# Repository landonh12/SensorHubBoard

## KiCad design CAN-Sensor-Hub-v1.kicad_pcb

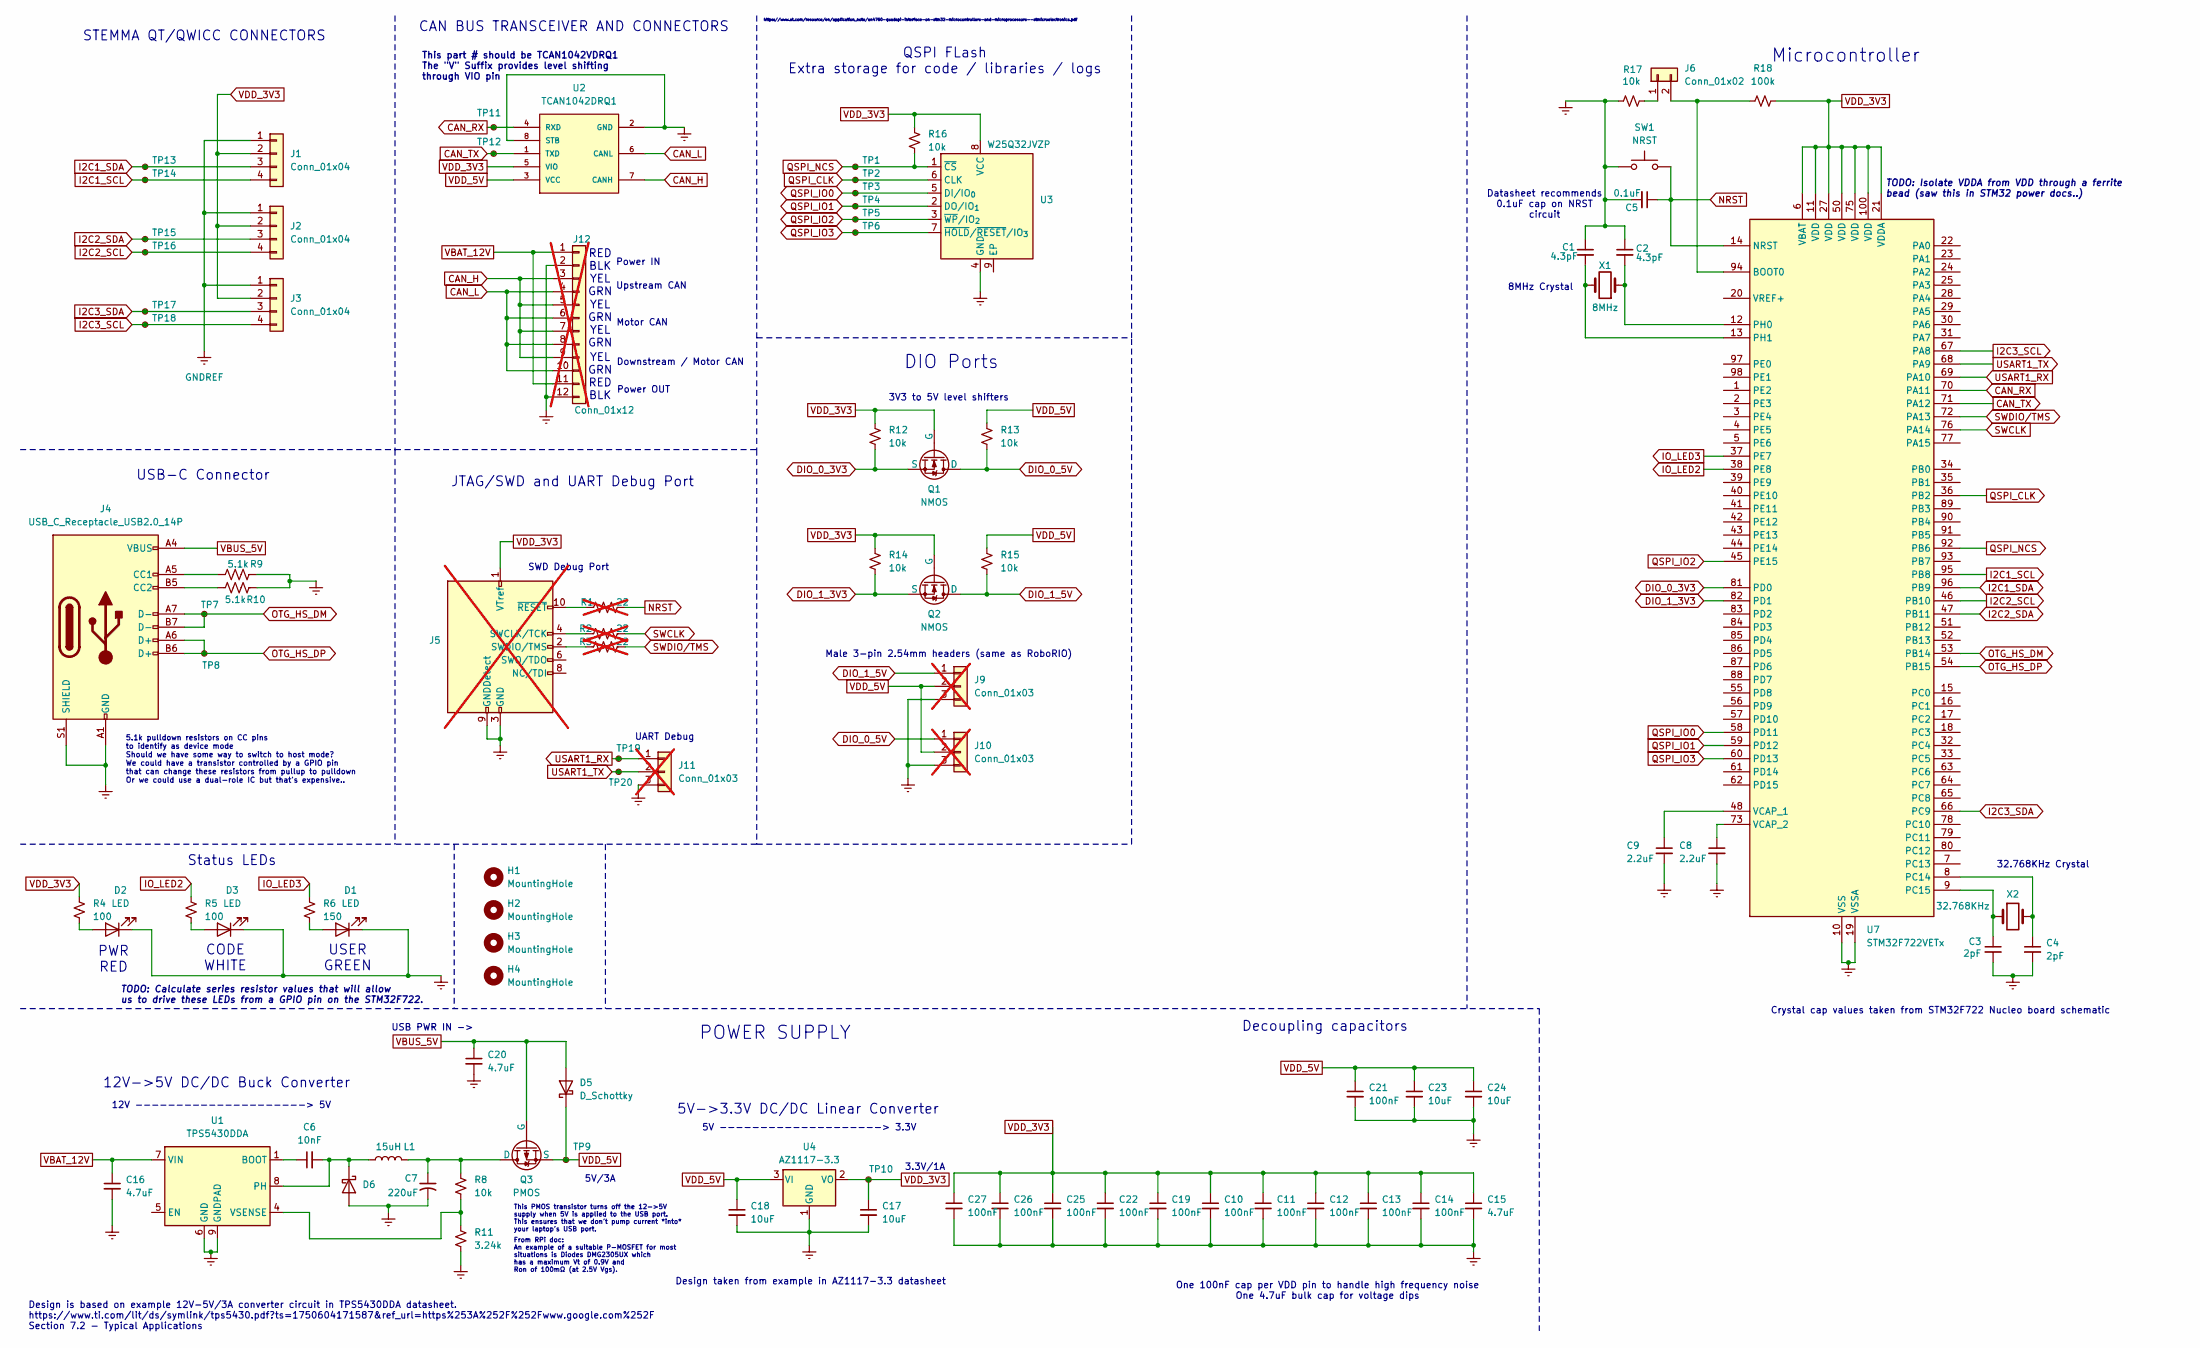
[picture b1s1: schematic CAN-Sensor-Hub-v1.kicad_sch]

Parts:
C1, C2: 4.3pF; C_0402_1005Metric; LCSC CL05C100JB5NNNC
C3, C4: 2pF; C_0402_1005Metric; LCSC 0402CG2R0C500NT
C5: 0.1uF; C_0402_1005Metric; LCSC CL05B104KO5NNNC
C6: 10nF; C_0402_1005Metric; LCSC CL05B103KB5NNNC
C7: 220uF; CP_EIA-3528-21_Kemet-B
C8, C9: 2.2uF; C_0402_1005Metric; LCSC CL05A225MQ5NSNC
C10, C11, C12, C13, C14, C19, C21, C22, C25, C26, C27: 100nF; C_0402_1005Metric; LCSC CL05B104KO5NNNC
C15, C20: 4.7uF; C_0603_1608Metric; LCSC CL10A475KO8NNNC
C16: 4.7uF; C_0805_2012Metric; LCSC CL21A475KAQNNNE
C17, C18, C23, C24: 10uF; C_0603_1608Metric; LCSC CL10A106MA8NRNC
D1: LED; LED_0805_2012Metric; LCSC KT-0805G
D2: LED; LED_0805_2012Metric; LCSC NCD0805R1
D3: LED; LED_0805_2012Metric; LCSC KT-0805W
D5, D6: D_Schottky; D_0603_1608Metric; LCSC SD0603S040S0R2
H1, H2, H3, H4: MountingHole; MountingHole_2.7mm_M2.5
J1, J2, J3: Conn_01x04; JST_SH_SM04B-SRSS-TB_1x04-1MP_P1.00mm_Horizontal; LCSC SM04B-SRSS-TB(LF)(SN)
J4: USB_C_Receptacle_USB2.0_14P; USB_C_Receptacle_GCT_USB4110; LCSC TYPEC-304YSSW-ACP16
J5: Conn_ARM_JTAG_SWD_10; PinHeader_2x05_P1.27mm_Vertical_SMD; not fitted
J6: Conn_01x02; PinHeader_1x02_P2.54mm_Vertical
J9, J10: Conn_01x03; PinHeader_1x03_P2.54mm_Horizontal; not fitted
J11: Conn_01x03; PinHeader_1x03_P2.54mm_Vertical; not fitted
J12: Conn_01x12; TerminalBlock_WAGO_2601-1112_1x12_P3.50mm_Horizontal; not fitted
L1: 15uH; L_Sumida_CDMC6D28_7.25x6.5mm; LCSC CYA0650-15UH
Q1, Q2: NMOS; SOT-23; LCSC SI2301CDS-T1-GE3
Q3: PMOS; SOT-23; LCSC AO3401A
R1, R2, R3: 22; R_0805_2012Metric; not fitted
R4, R5: 100; R_0402_1005Metric; LCSC 0402WGF1000TCE
R6: 150; R_0402_1005Metric; LCSC 0402WGF1500TCE
R8, R12, R13, R14, R15, R17: 10k; R_0402_1005Metric; LCSC 0402WGF1002TCE
R9, R10: 5.1k; R_0402_1005Metric; LCSC 0402WGF5101TCE
R11: 3.24k; R_0402_1005Metric; LCSC 0402WGF3241TCE
R16: 10k; R_0402_1005Metric
R18: 100k; R_0402_1005Metric; LCSC 0402WGF1002TCE
SW1: NRST; SW_TS-1088-AR02016; LCSC TS-1088-AR02016
TP1, TP2, TP3, TP4, TP5, TP6, TP7, TP8, TP9, TP10, TP11, TP12, TP13, TP14, TP15, TP16, TP17, TP18, TP19, TP20: TestPoint_Small; TestPoint_Pad_D0.5mm
U1: TPS5430DDA; TI_SO-PowerPAD-8_ThermalVias; LCSC TPS5430DDAR
U2: TCAN1042DRQ1; SOIC-8_3.9x4.9mm_P1.27mm; PARTNUMBER TCAN1042DRQ1
U3: W25Q32JVZP; WSON-8-1EP_6x5mm_P1.27mm_EP3.4x4.3mm; LCSC W25Q32JVZPIQ
U4: AZ1117-3.3; SOT-223-3_TabPin2; LCSC AMS1117-3.3
U7: STM32F722VETx; LQFP-100_14x14mm_P0.5mm; LCSC STM32F722VET6
X1: 8MHz; Crystal_SMD_3225-2Pin_3.2x2.5mm; LCSC NX3225GD-8MHZ-STD-CRA-3
X2: 32.768KHz; Crystal_SMD_3215-2Pin_3.2x1.5mm; LCSC NX3215SA-32.768K-STD-MUA-14

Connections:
CAN_H: J12.3, J12.5, J12.7, J12.9, U2.7 (CANH)
CAN_L: J12.4, J12.6, J12.8, J12.10, U2.6 (CANL)
CAN_RX: TP11.1, U2.4 (RXD), U7.70 (PA11)
CAN_TX: TP12.1, U2.1 (TXD), U7.71 (PA12)
DIO_0_3V3: Q1.3 (S), R12.2, U7.81 (PD0)
DIO_0_5V: J10.1, Q1.1 (D), R13.2
DIO_1_3V3: Q2.3 (S), R14.2, U7.82 (PD1)
DIO_1_5V: J9.1, Q2.1 (D), R15.2
GNDREF: C1.1, C2.1, C3.2, C4.2, C5.2, C7.2, C8.2, C9.2, C10.2, C11.2, C12.2, C13.2, C14.2, C15.2, C16.2, C17.2, C18.2, C19.2, C20.2, C21.2, C22.2, C23.2, C24.2, C25.2, C26.2, C27.2, D1.1 (K), D2.1 (K), D3.1 (K), D6.2 (A), J1.1, J2.1, J3.1, J4.A1 (GND), J4.A12 (GND), J4.B1 (GND), J4.B12 (GND), J4.S1 (SHIELD), J5.3 (GND), J5.5 (GND), J5.9 (GNDDetect), J9.3, J10.3, J11.3, J12.2, J12.12, R9.2, R10.2, R11.2, R17.1, SW1.1, U1.6 (GND), U1.9 (GNDPAD), U2.2 (GND), U2.8 (STB), U3.4 (GND), U4.1 (GND), U7.10 (VSS), U7.19 (VSSA), U7.26 (VSS), U7.49 (VSS), U7.74 (VSS), U7.99 (VSS)
I2C1_SCL: J1.4, TP14.1, U7.95 (PB8)
I2C1_SDA: J1.3, TP13.1, U7.96 (PB9)
I2C2_SCL: J2.4, TP16.1, U7.46 (PB10)
I2C2_SDA: J2.3, TP15.1, U7.47 (PB11)
I2C3_SCL: J3.4, TP18.1, U7.67 (PA8)
I2C3_SDA: J3.3, TP17.1, U7.66 (PC9)
IO_LED1: U7.39 (PE9)
IO_LED2: R5.1, U7.38 (PE8)
IO_LED3: R6.1, U7.37 (PE7)
NRST: C5.1, R1.2, SW1.2, U7.14 (NRST)
unnamed: D1.2 (A), R6.2
unnamed: D2.2 (A), R4.2
unnamed: D3.2 (A), R5.2
unnamed: C6.2, D6.1 (K), L1.1, U1.8 (PH)
unnamed: J4.A5 (CC1), R9.1
unnamed: J4.B5 (CC2), R10.1
unnamed: J5.4 (SWCLK/TCK), R2.1
unnamed: J5.2 (SWDIO/TMS), R3.1
unnamed: J5.10 (~RESET), R1.1
unnamed: J6.1, R17.2
unnamed: J6.2, R18.1, U7.94 (BOOT0)
unnamed: C7.1, L1.2, Q3.1 (D), R8.1
unnamed: C6.1, U1.1 (BOOT)
unnamed: R8.2, R11.1, U1.4 (VSENSE)
unnamed: C4.1, U7.8 (PC14), X2.2
unnamed: C3.1, U7.9 (PC15), X2.1
unnamed: C2.2, U7.12 (PH0), X1.1
unnamed: C1.2, U7.13 (PH1), X1.2
unnamed: C9.1, U7.48 (VCAP_1)
unnamed: C8.1, U7.73 (VCAP_2)
OTG_HS_DM: J4.A7 (D-), J4.B7 (D-), TP7.1, U7.53 (PB14)
OTG_HS_DP: J4.A6 (D+), J4.B6 (D+), TP8.1, U7.54 (PB15)
QSPI_CLK: TP2.1, U3.6 (CLK), U7.36 (PB2)
QSPI_IO0: TP3.1, U3.5 (DI/IO_{0}), U7.58 (PD11)
QSPI_IO1: TP4.1, U3.2 (DO/IO_{1}), U7.59 (PD12)
QSPI_IO2: TP5.1, U3.3 (~WP/IO_{2}), U7.45 (PE15)
QSPI_IO3: TP6.1, U3.7 (~HOLD/~RESET/IO_{3}), U7.60 (PD13)
QSPI_NCS: R16.2, TP1.1, U3.1 (~CS), U7.92 (PB6)
SWCLK: R2.2, U7.76 (PA14)
SWDIO/TMS: R3.2, U7.72 (PA13)
USART1_RX: J11.1, TP19.1, U7.69 (PA10)
USART1_TX: J11.2, TP20.1, U7.68 (PA9)
VBAT_12V: C16.1, J12.1, J12.11, U1.7 (VIN)
VBUS_5V: C20.1, D5.2 (A), J4.A4 (VBUS), J4.A9 (VBUS), J4.B4 (VBUS), J4.B9 (VBUS), Q3.2 (G)
VDD_3V3: C10.1, C11.1, C12.1, C13.1, C14.1, C15.1, C17.1, C19.1, C22.1, C25.1, C26.1, C27.1, J1.2, J2.2, J3.2, J5.1 (VTref), Q1.2 (G), Q2.2 (G), R4.1, R12.1, R14.1, R16.1, R18.2, TP10.1, U2.5 (VIO), U3.8 (VCC), U4.2 (VO), U7.6 (VBAT), U7.11 (VDD), U7.21 (VDDA), U7.27 (VDD), U7.50 (VDD), U7.75 (VDD), U7.100 (VDD)
VDD_5V: C18.1, C21.1, C23.1, C24.1, D5.1 (K), J9.2, J10.2, Q3.3 (S), R13.1, R15.1, TP9.1, U2.3 (VCC), U4.3 (VI)

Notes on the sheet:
Datasheet recommends 0.1uF cap on NRST circuit
Microcontroller
8MHz Crystal
3V3 to 5V level shifters
5V --------------------> 3.3V
Motor CAN
Decoupling capacitors
YEL GRN RED BLK
USB-C Connector
Power OUT
PWR RED
12V ---------------------> 5V
5.1k pulldown resistors on CC pins to identify as device mode Should we have some way to switch to host mode? We could have a transistor controlled by a GPIO pin that can change these resistors from pullup to pulldown Or we could use a dual-role IC but that's expensive..
Status LEDs
TODO: Isolate VDDA from VDD through a ferrite bead (saw this in STM32 power docs..)
UART Debug
One 100nF cap per VDD pin to handle high frequency noise One 4.7uF bulk cap for voltage dips
RED BLK YEL GRN
Power IN
Design is based on example 12V-5V/3A converter circuit in TPS5430DDA datasheet. https://www.ti.com/lit/ds/symlink/tps5430.pdf?ts=1750604171587&ref_url=https%253A%252F%252Fwww.google.com%252F Section 7.2 - Typical Applications
USB PWR IN ->
This PMOS transistor turns off the 12->5V supply when 5V is applied to the USB port. This ensures that we don't pump current *into* your laptop's USB port.
STEMMA QT/QWICC CONNECTORS
CODE WHITE
This part # should be TCAN1042VDRQ1 The "V" Suffix provides level shifting through VIO pin
DIO Ports
QSPI FLash Extra storage for code / libraries / logs
3.3V/1A
Design taken from example in AZ1117-3.3 datasheet
CAN BUS TRANSCEIVER AND CONNECTORS
32.768KHz Crystal
5V->3.3V DC/DC Linear Converter
USER GREEN
https://www.st.com/resource/en/application_note/an4760-quadspi-interface-on-stm32-microcontrollers-and-microprocessors--stmicroelectronics.pdf
YEL GRN YEL GRN
5V/3A
POWER SUPPLY
JTAG/SWD and UART Debug Port
Upstream CAN
Downstream / Motor CAN

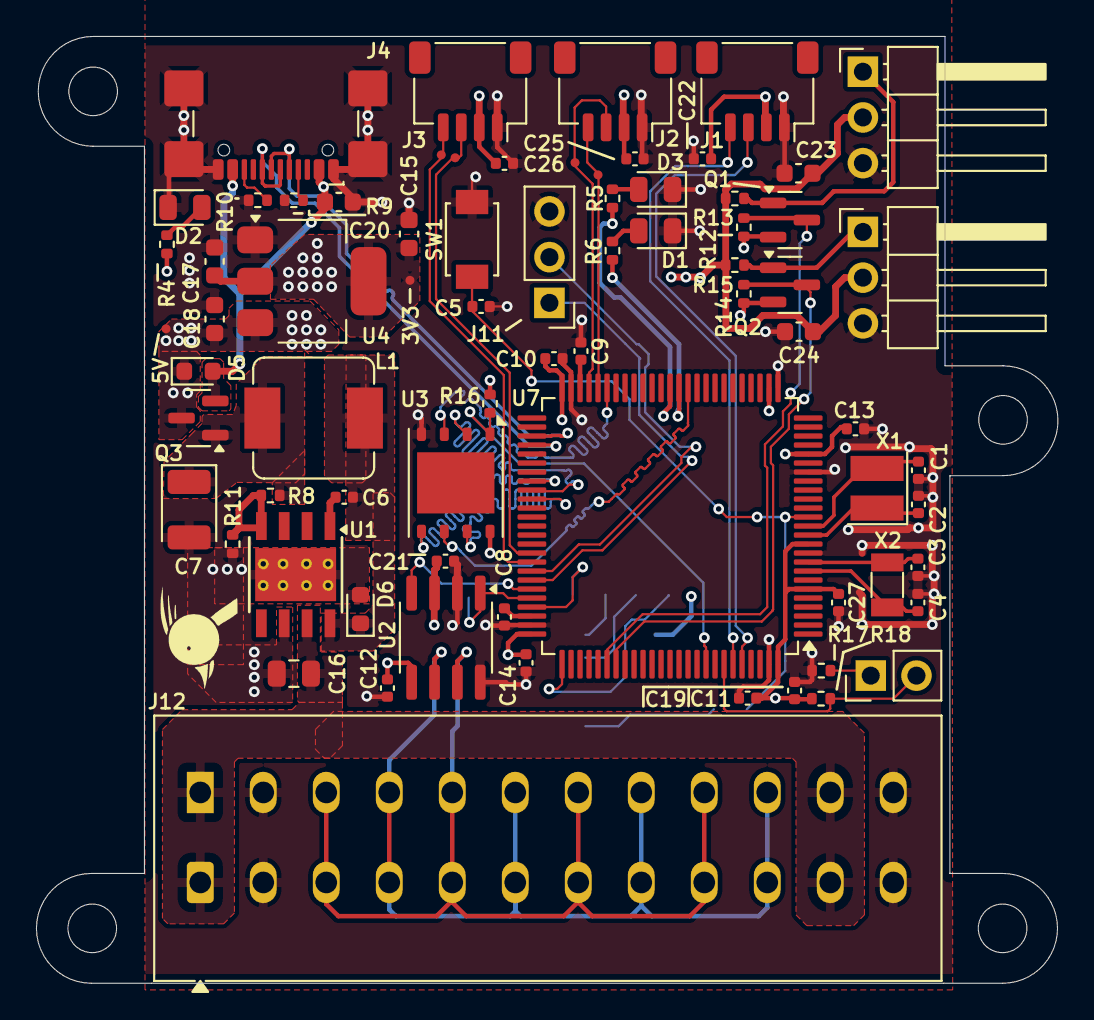
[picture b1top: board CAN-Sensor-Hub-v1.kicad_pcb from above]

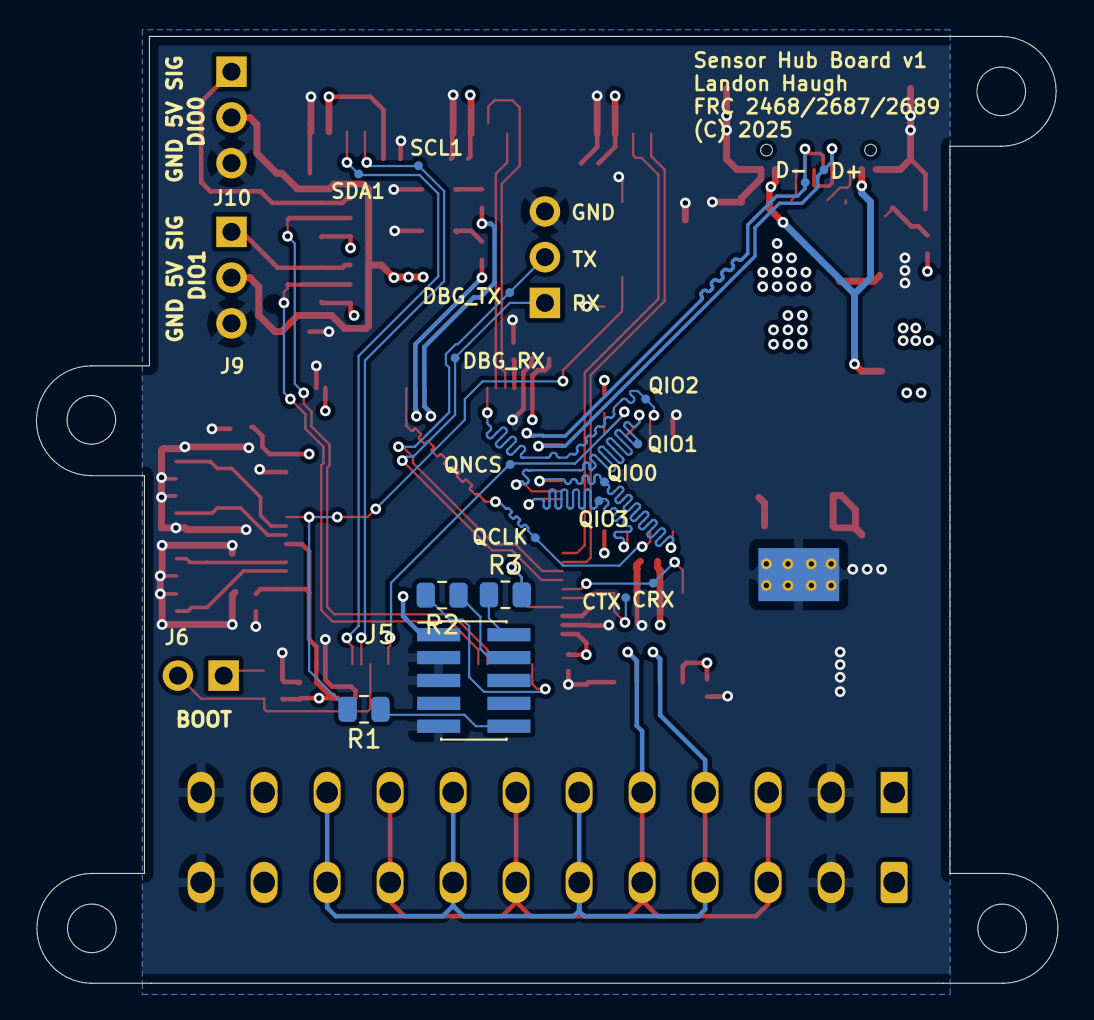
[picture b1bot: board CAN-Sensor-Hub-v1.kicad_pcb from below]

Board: 4 copper layers, 56.8 x 52.6 mm, 95 parts (18 on the bottom side), 54 nets.

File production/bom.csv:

Designator,Footprint,Quantity,Value,LCSC Part #
"C1, C2",0402,2,4.3pF,CL05C100JB5NNNC
"C10, C11, C12, C13, C14, C19, C21, C22, C25, C26, C27",0402,11,100nF,CL05B104KO5NNNC
"C15, C20",0603,2,4.7uF,CL10A475KO8NNNC
C16,0805,1,4.7uF,CL21A475KAQNNNE
"C17, C18, C23, C24",0603,4,10uF,CL10A106MA8NRNC
"C3, C4",0402,2,2pF,0402CG2R0C500NT
C5,0402,1,0.1uF,CL05B104KO5NNNC
C6,0402,1,10nF,CL05B103KB5NNNC
C7,CP_EIA-3528-21_Kemet-B,1,220uF,
"C8, C9",0402,2,2.2uF,CL05A225MQ5NSNC
D1,0805,1,LED,KT-0805G
D2,0805,1,LED,NCD0805R1
D3,0805,1,LED,KT-0805W
"D5, D6",0603,2,D_Schottky,SD0603S040S0R2
"J1, J2, J3",JST_SH_SM04B-SRSS-TB_1x04-1MP_P1.00mm_Horizontal,3,Conn_01x04,SM04B-SRSS-TB(LF)(SN)
J4,USB_C_Receptacle_GCT_USB4110,1,USB_C_Receptacle_USB2.0_14P,TYPEC-304YSSW-ACP16
J6,PinHeader_1x02_P2.54mm_Vertical,1,Conn_01x02,
L1,L_Sumida_CDMC6D28_7.25x6.5mm,1,15uH, CYA0650-15UH
"Q1, Q2",SOT-23,2,NMOS, SI2301CDS-T1-GE3
Q3,SOT-23,1,PMOS, AO3401A
"R10, R9",0402,2,5.1k,0402WGF5101TCE
R11,0402,1,3.24k, 0402WGF3241TCE
"R12, R13, R14, R15, R17, R8",0402,6,10k, 0402WGF1002TCE
R16,0402,1,10k,
R18,0402,1,100k, 0402WGF1002TCE
"R4, R5",0402,2,100,0402WGF1000TCE
R6,0402,1,150,0402WGF1500TCE
SW1,SW_TS-1088-AR02016,1,NRST,TS-1088-AR02016
"TP1, TP10, TP11, TP12, TP13, TP14, TP15, TP16, TP17, TP18, TP19, TP2, TP20, TP3, TP4, TP5, TP6, TP7, TP8, TP9",TestPoint_Pad_D0.5mm,20,TestPoint_Small,
U1,TI_SO-PowerPAD-8_ThermalVias,1,TPS5430DDA,TPS5430DDAR
U2,SOIC-8_3.9x4.9mm_P1.27mm,1,TCAN1042DRQ1,https://jlcpcb.com/partdetail/TexasInstruments-TCAN1042VDRQ1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
U3,WSON-8-1EP_6x5mm_P1.27mm_EP3.4x4.3mm,1,W25Q32JVZP,W25Q32JVZPIQ
U4,SOT-223-3_TabPin2,1,AZ1117-3.3,AMS1117-3.3
U7,LQFP-100_14x14mm_P0.5mm,1,STM32F722VETx,STM32F722VET6
X1,Crystal_SMD_3225-2Pin_3.2x2.5mm,1,8MHz, NX3225GD-8MHZ-STD-CRA-3
X2,Crystal_SMD_3215-2Pin_3.2x1.5mm,1,32.768KHz,NX3215SA-32.768K-STD-MUA-14

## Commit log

2025-06-22 Cleaned up schematic, added 5V->3V linear converter
2025-06-24 Updated schematic, added PCB file with footprints assigned and started experimenting
2025-06-27 Initial prototype layout done - likely needs to be redone
2025-07-01 V0.2 of board, nearly ready for production
2025-07-02 Production ready board
2025-07-02 Made some more adjustments .. USART2 is not compatible with bootloader, changed to USART1

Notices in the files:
CAN-Sensor-Hub-v1.kicad_pcb:
(C) 2025
